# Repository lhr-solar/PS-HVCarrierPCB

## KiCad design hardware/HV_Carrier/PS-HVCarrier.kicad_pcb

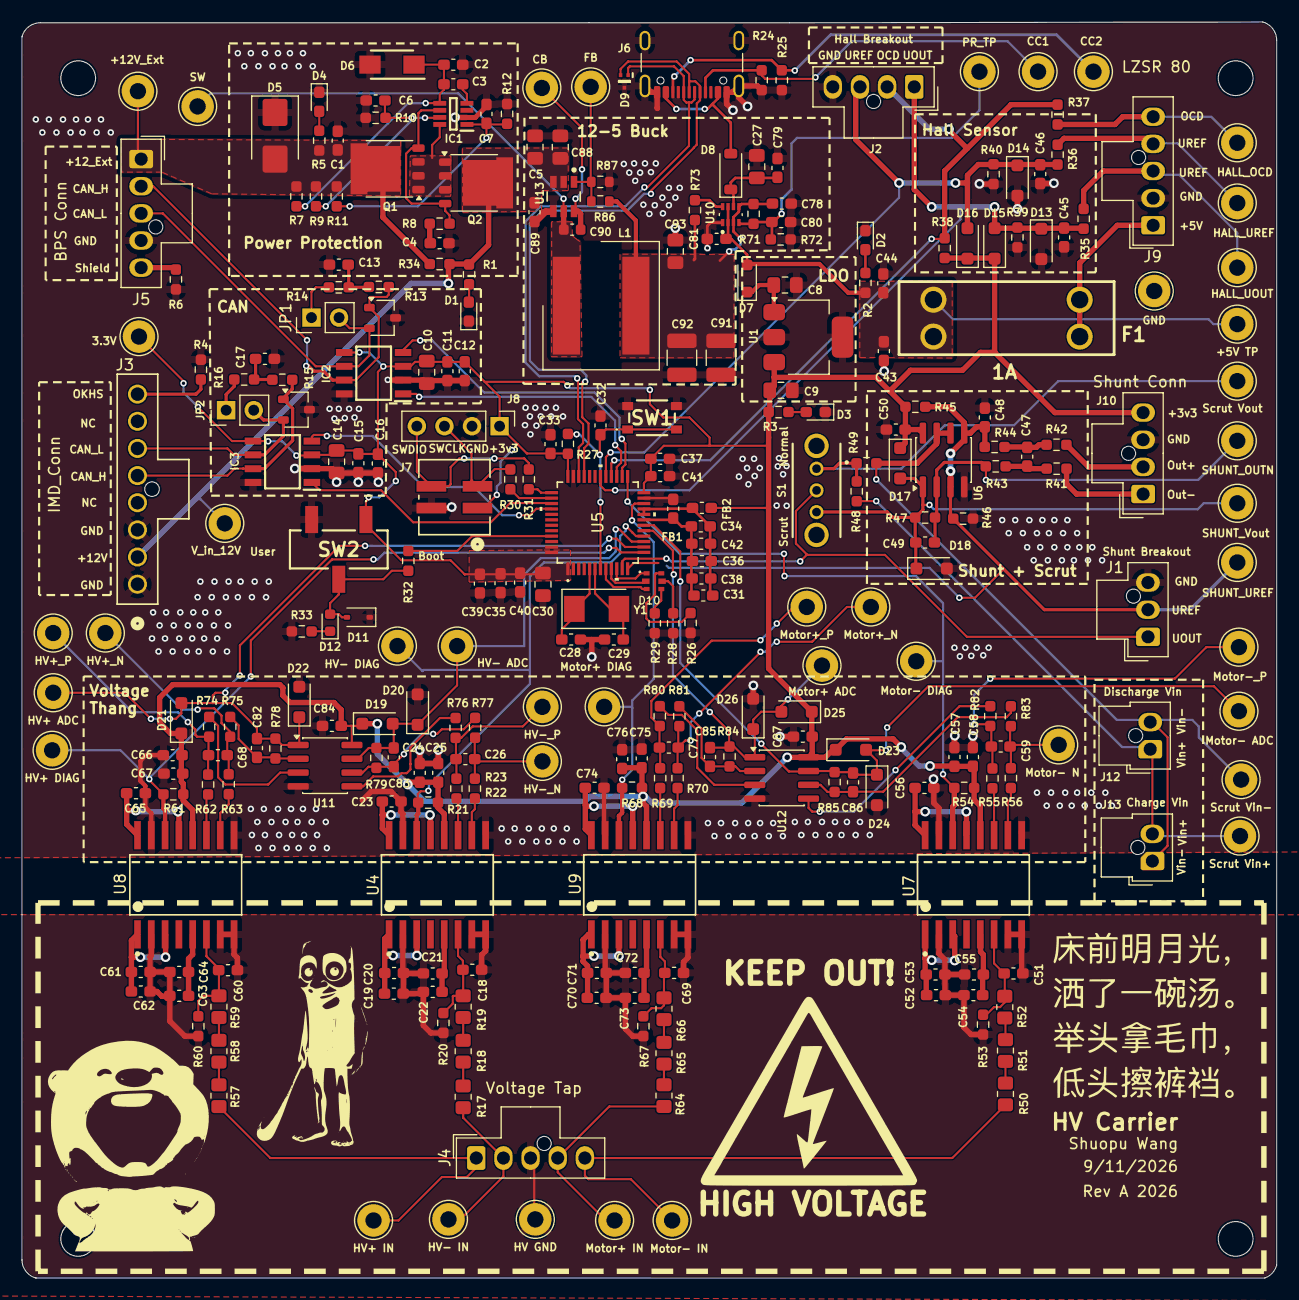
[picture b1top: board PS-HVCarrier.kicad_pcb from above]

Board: 2 copper layers, 115.6 x 115.7 mm, 291 parts (0 on the bottom side), 140 nets.

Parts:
C1, C6, C7, C11, C12, C13, C15, C16, C17, C50, C84, C87: 0.1u; C_0603_1608Metric_Pad1.08x0.95mm_HandSolder
C2, C25, C44, C58, C67, C76: 1u; C_0603_1608Metric_Pad1.08x0.95mm_HandSolder
C3: 220n; C_0603_1608Metric_Pad1.08x0.95mm_HandSolder
C4, C26, C45, C46, C59, C68, C77: 10n; C_0603_1608Metric_Pad1.08x0.95mm_HandSolder
C5, C8, C9, C10, C14, C27, C30: 10u; C_0805_2012Metric_Pad1.18x1.45mm_HandSolder
C18, C51, C60, C69: 100p; C_0603_1608Metric_Pad1.08x0.95mm_HandSolder
C19, C22, C24, C49, C52, C55, C57, C61, C64, C66, C70, C73, C75, C82, C83, C85, C86: 1n; C_0603_1608Metric_Pad1.08x0.95mm_HandSolder
C20, C21, C23, C42, C43, C47, C48, C53, C54, C56, C62, C63, C65, C71, C72, C74, C89: 100n; C_0603_1608Metric_Pad1.08x0.95mm_HandSolder
C28, C29: 26p; C_0603_1608Metric_Pad1.08x0.95mm_HandSolder
C31, C32, C33, C34, C35, C37, C39, C40, C41, C78, C79, C80, C81: 0.1uF; C_0603_1608Metric_Pad1.08x0.95mm_HandSolder
C36, C38: 1uF; C_0603_1608Metric_Pad1.08x0.95mm_HandSolder
C88: 4.7u; C_0805_2012Metric_Pad1.18x1.45mm_HandSolder
C90: 100n; C_0603_1608Metric
C91, C92: 22u; C_1210_3225Metric_Pad1.33x2.70mm_HandSolder
C93: 3.3u; C_0805_2012Metric_Pad1.18x1.45mm_HandSolder
D1, D2, D3, D4: LED; LED_0603_1608Metric_Pad1.05x0.95mm_HandSolder
D5: SMBJ15CA; D_SMB
D6: SMAF4758A; SODFL5026X125N
D7: SBA130CH-AU_R1_000A1; D_SOD-323_HandSoldering
D8: D_Schottky; D_SOD-123
D9: TPD2EUSB30DRTR
D10: RGB_LED
D11: TVS; D_SOD-323
D12: LED; LED_0603_1608Metric
D13, D14, D15, D16: D_SOD-123F
D17, D18, D19, D20, D21, D22, D23, D24, D25, D26: TVS; D_SOD-123F
F1: 1A; Fuse-3557-2
FB1, FB2: FerriteBead; C_0603_1608Metric_Pad1.08x0.95mm_HandSolder
H1, H2, H3, H4: MountingHole; MountingHole_3.2mm_M3
IC1: LM74502DDFR
IC2, IC3: TCAN3413DR
J1: Shunt Breakout; Molex_Nano-Fit_105309-xx03_1x03_P2.50mm_Vertical
J2: Hall Breakout; Molex_Nano-Fit_105309-xx04_1x04_P2.50mm_Vertical
J3: IMD_Conn; CONN_SD-105309-100_08_MOL
J4: Voltage Tap; Molex_Nano-Fit_105309-xx05_1x05_P2.50mm_Vertical
J5: BPS Conn; Molex_Nano-Fit_105309-xx05_1x05_P2.50mm_Vertical
J6: USB_C_Receptacle_USB2.0_16P; USB_C_Receptacle_GCT_USB4105-xx-A_16P_TopMnt_Horizontal
J7: SWD_Header; SWD_Conn
J8: SWD; PinHeader_1x04_P2.54mm_Vertical
J9: LZSR 80; Molex_Nano-Fit_105309-xx05_1x05_P2.50mm_Vertical
J10: Shunt Conn; Molex_Nano-Fit_105309-xx04_1x04_P2.50mm_Vertical
J12: Discharge Vin; Molex_Nano-Fit_105309-xx02_1x02_P2.50mm_Vertical
J13: Charge Vin; Molex_Nano-Fit_105309-xx02_1x02_P2.50mm_Vertical
JP1, JP2: TRM; PinHeader_1x02_P2.54mm_Vertical
L1: 8.2u; 74439369082
Q1, Q2: PSMN012-100YS; LFPAK56
R1, R5: 470; R_0603_1608Metric_Pad0.98x0.95mm_HandSolder
R2, R3: 150; R_0603_1608Metric_Pad0.98x0.95mm_HandSolder
R4: 2.1k; R_0603_1608Metric_Pad0.98x0.95mm_HandSolder
R6, R34: 0; R_0603_1608Metric_Pad0.98x0.95mm_HandSolder
R7, R27, R32, R35, R36, R37, R43, R44, R47, R49, R73, R74, R75, R76, R77, R78, R79, R80, R81, R82, R83, R84, R85: 10k; R_0603_1608Metric_Pad0.98x0.95mm_HandSolder
R8: 33; R_0603_1608Metric_Pad0.98x0.95mm_HandSolder
R9, R11: 100k; R_0603_1608Metric_Pad0.98x0.95mm_HandSolder
R10: 7.32k; R_0603_1608Metric_Pad0.98x0.95mm_HandSolder
R12: 15.8k; R_0603_1608Metric_Pad0.98x0.95mm_HandSolder
R13, R14, R15, R16: 60; R_0603_1608Metric_Pad0.98x0.95mm_HandSolder
R17, R18, R19, R50, R51, R52, R57, R58, R59, R64, R65, R66: 500k; R_0805_2012Metric_Pad1.20x1.40mm_HandSolder
R20, R38, R39, R40, R45, R46, R53, R60, R67: 20k; R_0603_1608Metric_Pad0.98x0.95mm_HandSolder
R21, R54, R61, R68: 47k; R_0603_1608Metric_Pad0.98x0.95mm_HandSolder
R22, R23, R55, R56, R62, R63, R69, R70: 10; R_0603_1608Metric_Pad0.98x0.95mm_HandSolder
R24, R25: 5.1k; R_0603_1608Metric_Pad0.98x0.95mm_HandSolder
R26, R28, R29, R33: 1k; R_0603_1608Metric_Pad0.98x0.95mm_HandSolder
R30, R31: 22; R_0603_1608Metric_Pad0.98x0.95mm_HandSolder
R41, R42: 100; R_0603_1608Metric_Pad0.98x0.95mm_HandSolder
R48: 90k; R_0603_1608Metric_Pad0.98x0.95mm_HandSolder
R71: 16k; R_0603_1608Metric_Pad0.98x0.95mm_HandSolder
R72: 4.7k; R_0603_1608Metric_Pad0.98x0.95mm_HandSolder
R86: 100k; R_0603_1608Metric
R87: 19.1k; R_0603_1608Metric
S1: OS102011MS2QN1; OS102011MA1QN1
SW1: Reset; TL3365AF180QG
SW2: SW_SPDT; BootSW
TP1: HV GND; TestPoint_THTPad_D3.0mm_Drill1.5mm
TP3: +5V TP; TestPoint_THTPad_D3.0mm_Drill1.5mm
TP4: GND; TestPoint_THTPad_D3.0mm_Drill1.5mm
TP5: +12V_Ext; TestPoint_THTPad_D3.0mm_Drill1.5mm
TP7: CC1; TestPoint_THTPad_D3.0mm_Drill1.5mm
TP8: CC2; TestPoint_THTPad_D3.0mm_Drill1.5mm
TP9: PR_TP; TestPoint_THTPad_D3.0mm_Drill1.5mm
TP10: HALL_UOUT; TestPoint_THTPad_D3.0mm_Drill1.5mm
TP11: HALL_UREF; TestPoint_THTPad_D3.0mm_Drill1.5mm
TP12: HALL_OCD; TestPoint_THTPad_D3.0mm_Drill1.5mm
TP13: SHUNT_OUTN; TestPoint_THTPad_D3.0mm_Drill1.5mm
TP14: SHUNT_UREF; TestPoint_THTPad_D3.0mm_Drill1.5mm
TP15: Scrut Vin+; TestPoint_THTPad_D3.0mm_Drill1.5mm
TP16: Scrut Vout; TestPoint_THTPad_D3.0mm_Drill1.5mm
TP17: Scrut Vin-; TestPoint_THTPad_D3.0mm_Drill1.5mm
TP18: SHUNT_Vout; TestPoint_THTPad_D3.0mm_Drill1.5mm
TP19: HV+ IN; TestPoint_THTPad_D3.0mm_Drill1.5mm
TP20: Motor+ IN; TestPoint_THTPad_D3.0mm_Drill1.5mm
TP21: HV+_P; TestPoint_THTPad_D3.0mm_Drill1.5mm
TP22: HV+_N; TestPoint_THTPad_D3.0mm_Drill1.5mm
TP23: Motor+_P; TestPoint_THTPad_D3.0mm_Drill1.5mm
TP24: Motor+_N; TestPoint_THTPad_D3.0mm_Drill1.5mm
TP25: HV+ DIAG; TestPoint_THTPad_D3.0mm_Drill1.5mm
TP26: Motor+ DIAG; TestPoint_THTPad_D3.0mm_Drill1.5mm
TP27: Motor- IN; TestPoint_THTPad_D3.0mm_Drill1.5mm
TP28: HV- IN; TestPoint_THTPad_D3.0mm_Drill1.5mm
TP29: HV-_P; TestPoint_THTPad_D3.0mm_Drill1.5mm
TP30: HV-_N; TestPoint_THTPad_D3.0mm_Drill1.5mm
TP31: Motor-_P; TestPoint_THTPad_D3.0mm_Drill1.5mm
TP32: Motor- N; TestPoint_THTPad_D3.0mm_Drill1.5mm
TP33: HV- DIAG; TestPoint_THTPad_D3.0mm_Drill1.5mm
TP34: Motor- DIAG; TestPoint_THTPad_D3.0mm_Drill1.5mm
TP35: HV- ADC; TestPoint_THTPad_D3.0mm_Drill1.5mm
TP36: HV+ ADC; TestPoint_THTPad_D3.0mm_Drill1.5mm
TP37: Motor+ ADC; TestPoint_THTPad_D3.0mm_Drill1.5mm
TP38: Motor- ADC; TestPoint_THTPad_D3.0mm_Drill1.5mm
TP39: V_in_12V; TestPoint_THTPad_D3.0mm_Drill1.5mm
TP40: CB; TestPoint_THTPad_D3.0mm_Drill1.5mm
TP41: FB; TestPoint_THTPad_D3.0mm_Drill1.5mm
TP42: SW; TestPoint_THTPad_D3.0mm_Drill1.5mm
TP_1: 3.3V; TestPoint_THTPad_D3.0mm_Drill1.5mm
U1: MCP1826S; SOT-223-3_TabPin2
U2, U3: CDSOT23-T24CAN
U4, U7, U8, U9: AMC3311QDWERQ1; DWE0016A-IPC_A
U5: STM32G473CETx; 48PinMCU
U6, U11, U12: TLV9002QDRQ1; SOIC-8_3.9x4.9mm_P1.27mm
U10: TPS2117DRLR
U13: LMR51635XDDCR; DDC0006A-MFG
Y1: Crystal; Crystal_SMD_Abracon_ABM3-2Pin_5.0x3.2mm

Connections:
/48PinMCU/BOOT0: R32.1, U5.45 (PB8-BOOT0)
/48PinMCU/GNDA: C31.2, C34.2, C36.2, C38.2, C42.2, FB1.1, U5.19 (VSSA)
/48PinMCU/NRST: C32.1, R27.1, SW1.1, U5.7 (PG10-NRST)
/48PinMCU/PA0: D10.5, U5.8 (PA0-GPIO_BLUE)
/48PinMCU/PA1: D10.3, U5.9 (PA1_GPIO_RED)
/48PinMCU/PA2: D10.1, U5.10 (PA2-GPIO_GREEN)
/48PinMCU/SWCLK: R30.1, U5.38 (PA14)
/48PinMCU/SWDIO: R31.1, U5.37 (PA13)
/48PinMCU/VDDA: C31.1, C34.1, C36.1, C38.1, C42.1, FB2.2, U5.20 (VREF+), U5.21 (VDDA)
/+3v3: C9.2, C10.1, C11.1, C12.1, C14.1, C15.1, C16.1, C24.1, C25.1, C30.1, C33.1, C35.1, C37.1, C39.1, C40.1, C41.1, C50.1, C57.1, C58.1, C66.1, C67.1, C75.1, C76.1, C84.1, C87.1, D15.1 (K), D16.1 (K), D17.1 (K), D19.1 (K), D21.1 (K), D23.1 (K), D25.1 (K), FB2.1, IC2.3 (VCC), IC2.5 (SHDNV_IO), IC3.3 (VCC), IC3.5 (SHDNV_IO), J7.1, J8.1, J10.4 (PWR), R3.1, R21.1, R27.2, R38.2, R45.2, R54.1, R61.1, R68.1, SW2.1 (A), TP_1.1 (1_1), U1.3 (VO), U4.12 (VDD), U5.1 (VBAT), U5.24 (VDD), U5.36 (VDD), U5.48 (VDD), U6.8 (V+), U7.12 (VDD), U8.12 (VDD), U9.12 (VDD), U11.8 (V+), U12.8 (V+)
/+5V: C43.1, C44.1, C81.1, D7.2 (A), F1.1, R2.1, TP3.1 (1_1), U10.2 (VOUT), U10.7 (VOUT__1)
/+12V: C5.1, C88.1, C89.1, J3.2, Q2.5, R1.1, R34.2, TP39.1 (1_1), U13.2 (EN), U13.3 (VIN)
/+12V_Ext: C1.1, D5.2 (A2), J5.1 (12V), Q1.5, R5.1, R7.2, R9.1, R11.1, R34.1, TP5.1 (1_1)
/BPS_CAN_H: IC2.7 (CANH), J5.2 (CAN_H), R13.1, U2.1 (CAN_H)
/BPS_CAN_L: IC2.6 (CANL), J5.3 (CAN_L), JP1.2 (B), U2.2 (CAN_L)
/CAN1_RX: IC3.4 (RXD), U5.40 (PB3)
/CAN1_TX: IC3.1 (TXD), U5.39 (PA15)
/CAN2_RX: IC2.4 (RXD), U5.26 (PB12)
/CAN2_TX: IC2.1 (TXD), U5.27 (PB13)
/Current_Sense/LZSR_OCD: J9.5 (OCD), R37.2, TP12.1 (1_1)
/Current_Sense/LZSR_UOUT: J9.3 (UOUT), R35.2, TP10.1 (1_1)
/Current_Sense/LZSR_UREF: J9.4 (UREF), R36.2, TP11.1 (1_1)
/Current_Sense/SHUNT Vout: C49.1, D17.2 (A), D18.1 (K), R47.1, S1.3, TP18.1 (1_1), U6.1
/Current_Sense/Scrut Vout: R48.2, R49.1, S1.1, TP16.1 (1_1)
/Current_Sense/Vin+: J12.1, J13.2, R48.1, TP15.1 (1_1)
/Current_Sense/Vin-: J12.2, J13.1, R49.2, TP17.1 (1_1), U6.6 (-), U6.7
/HALL_OCD: J2.2 (UREF), R37.1, R38.1, U5.28 (PB14)
/HALL_UOUT: C45.1, D13.1 (K), D15.2 (A), J2.1 (UOUT), R35.1, R39.2, U5.30 (PA8)
/HALL_UREF: C46.1, D14.1 (K), D16.2 (A), J2.3 (GND), R36.1, R40.2, U5.29 (PB15)
/HV+: J4.1 (HV+), R57.1, TP19.1 (1_1)
/HV+_ADC: C82.2, D21.2 (A), D22.1 (K), R78.1, TP36.1 (1_1), U5.14 (PA6), U11.1
/HV+_DIAG: R61.2, TP25.1 (1_1), U5.13 (PA5), U8.14 (DIAG)
/HV-: J4.2 (HV-), R17.1, TP28.1 (1_1)
/HV-_ADC: C83.2, D19.2 (A), D20.1 (K), R79.1, TP35.1 (1_1), U5.15 (PA7), U11.7
/HV-_DIAG: R21.2, TP33.1 (1_1), U4.14 (DIAG), U5.16 (PB0)
/IMD_CAN_H: IC3.7 (CANH), J3.5, R15.1, U3.1 (CAN_H)
/IMD_CAN_L: IC3.6 (CANL), J3.6, JP2.2 (B), U3.2 (CAN_L)
/IMD_OKHS: J3.8, R4.2
/MOTOR+_ADC: C85.2, D25.2 (A), D26.1 (K), R84.1, TP37.1 (1_1), U5.17 (PB1), U12.1
/MOTOR+_DIAG: R68.2, TP26.1 (1_1), U5.22 (PB10), U9.14 (DIAG)
/MOTOR-_ADC: C86.2, D23.2 (A), D24.1 (K), R85.1, TP38.1 (1_1), U5.18 (PB2), U12.7
/MOTOR-_DIAG: R54.2, TP34.1 (1_1), U5.25 (PB11), U7.14 (DIAG)
/Motor_Precharge+: J4.4 (MOTOR+), R64.1, TP20.1 (1_1)
/Motor_Precharge-: J4.5 (MOTOR-), R50.1, TP27.1 (1_1)
/Power_Data/12VBuck/CB: C90.1, TP40.1 (1_1), U13.6 (CB)
/Power_Data/12VBuck/FB: R86.2, R87.1, TP41.1 (1_1), U13.1 (FB)
/Power_Data/12VBuck/SW: C90.2, L1.1, TP42.1 (1_1), U13.5 (SW)
/Power_Data/Buck_5V: C78.1, C91.1, C92.1, C93.1, L1.2, R71.1, R73.1, R86.1, U10.3 (VIN1), U10.5 (MODE)
/Power_Data/PowerProtection/EN/UVLO: C7.2, IC1.1 (EN/UVLO), R11.2, R12.2
/Power_Data/PowerProtection/OV: C6.2, IC1.7 (OV), R9.2, R10.1
/Power_Data/PowerProtection/gate: IC1.6 (GATE), Q1.4, Q2.4, R8.2
/Power_Data/PowerProtection/source: IC1.8 (SRC), Q1.1, Q1.2, Q1.3, Q2.1, Q2.2, Q2.3
/Power_Data/Power_Mux/PR1: C80.1, R71.2, R72.1, TP9.1 (1_1), U10.4 (PR1)
/Power_Data/Power_Mux/VIN_2: C27.2, C79.1, D8.1 (K), U10.6 (VIN2)
/Power_Data/USB-C Connector/CC1: J6.A5 (CC1), R24.2, TP7.1 (1_1)
/Power_Data/USB-C Connector/CC2: J6.B5 (CC2), R25.2, TP8.1 (1_1)
/Power_Data/USB-C Connector/VBUS_IN: D8.2 (A), J6.A4 (VBUS), J6.A9 (VBUS), J6.B4 (VBUS), J6.B9 (VBUS)
/SHUNT_UOUT: J1.1 (UOUT), S1.2, U5.11 (PA3)
/SHUNT_UREF: C48.1, J1.2 (UREF), R44.1, R45.1, R46.1, TP14.1 (1_1), U5.12 (PA4), U6.3 (+), U6.5 (+)
/USB_D+: D9.1 (D+), J6.A6 (D+), J6.B6 (D+), U5.34 (PA12)
/USB_D-: D9.2 (D-), J6.A7 (D-), J6.B7 (D-), U5.33 (PA11)
/Voltage_Sense/HV+_N: C68.1, R63.2, R75.1, TP22.1 (1_1)
/Voltage_Sense/HV+_P: C68.2, R62.2, R74.1, TP21.1 (1_1)
/Voltage_Sense/HV-_N: C26.1, R23.2, R77.1, TP30.1 (1_1)
/Voltage_Sense/HV-_P: C26.2, R22.2, R76.1, TP29.1 (1_1)
/Voltage_Sense/Motor+_N: C77.1, R70.2, R81.1, TP24.1 (1_1)
/Voltage_Sense/Motor+_P: C77.2, R69.2, R80.1, TP23.1 (1_1)
/Voltage_Sense/Motor-_N: C59.1, R56.2, R83.1, TP32.1 (1_1)
/Voltage_Sense/Motor-_P: C59.2, R55.2, R82.1, TP31.1 (1_1)
GND: C1.2, C2.1, C4.2, C5.2, C6.1, C7.1, C8.1, C9.1, C10.2, C11.2, C12.2, C13.2, C14.2, C15.2, C16.2, C17.2, C23.2, C24.2, C25.2, C27.1, C28.1, C29.2, C30.2, C32.2, C33.2, C35.2, C37.2, C39.2, C40.2, C41.2, C43.2, C44.2, C45.2, C46.2, C48.2, C50.2, C56.2, C57.2, C58.2, C65.2, C66.2, C67.2, C74.2, C75.2, C76.2, C78.2, C79.2, C80.2, C81.2, C84.2, C87.2, C88.2, C89.2, C91.2, C92.2, C93.2, D1.1 (K), D2.1 (K), D3.1 (K), D4.1 (K), D5.1 (A1), D6.2 (A), D9.3 (GND), D11.1 (A1), D13.2 (A), D14.2 (A), D18.2 (A), D20.2 (A), D22.2 (A), D24.2 (A), D26.2 (A), FB1.2, IC1.2 (GND), IC2.2 (GND), IC2.8 (STB), IC3.2 (GND), IC3.8 (STB), J1.3 (GND), J2.4 (GND), J3.1, J3.3, J5.4 (GND), J6.A1 (GND), J6.A12 (GND), J6.B1 (GND), J6.B12 (GND), J6.S1 (SHIELD), J6.S2 (Shield), J6.S3 (Shield), J6.S4 (Shield), J7.2, J8.2, J9.2 (GND), J10.3 (GND), R4.1, R6.1, R10.2, R12.1, R24.1, R25.1, R26.2, R28.2, R29.2, R33.2, R39.1, R40.1, R46.2, R72.2, R87.2, SW1.2, SW2.3 (C), TP4.1 (1_1), U1.2 (GND), U2.3 (GND), U3.3 (GND), U4.9 (GND), U4.15 (DCDC_GND), U5.23 (VSS), U5.35 (VSS), U5.47 (VSS), U6.4 (V-), U7.9 (GND), U7.15 (DCDC_GND), U8.9 (GND), U8.15 (DCDC_GND), U9.9 (GND), U9.15 (DCDC_GND), U10.1 (GND), U11.4 (V-), U12.4 (V-), U13.4 (GND)
HV GND: C18.2, C19.2, C20.1, C21.1, C22.1, C51.2, C52.2, C53.1, C54.1, C55.1, C60.2, C61.2, C62.1, C63.1, C64.1, C69.2, C70.2, C71.1, C72.1, C73.1, J4.3 (GND), R20.1, R53.1, R60.1, R67.1, TP1.1 (1_1), U4.2 (DCDC_HGND), U4.7 (HGND), U4.8 (HGND), U7.2 (DCDC_HGND), U7.7 (HGND), U7.8 (HGND), U8.2 (DCDC_HGND), U8.7 (HGND), U8.8 (HGND), U9.2 (DCDC_HGND), U9.7 (HGND), U9.8 (HGND)
unnamed: C4.1, R8.1
unnamed: C13.1, R13.2, R14.1
unnamed: C17.1, R15.2, R16.1
unnamed: C47.1, R41.1, R43.2
unnamed: C47.2, R42.1, R44.2
unnamed: D1.2 (A), R1.2
unnamed: D2.2 (A), R2.2
unnamed: D3.2 (A), R3.2
unnamed: D4.2 (A), R5.2
unnamed: C2.2, C3.1, D6.1 (K), IC1.5 (VS), R7.1
unnamed: C8.2, D7.1 (K), U1.1 (VI)
unnamed: D10.2, R26.1
unnamed: D10.4, R28.1
unnamed: D10.6, R29.1
unnamed: D11.2 (A2), D12.2 (A), R32.2, SW2.2 (B)
unnamed: D12.1 (K), R33.1
unnamed: C3.2, IC1.4 (VCAP)
unnamed: J5.5 (SHIELD), R6.2
unnamed: J7.3, J8.3, R30.2
unnamed: J7.4, J8.4, R31.2
unnamed: F1.2, J9.1 (+UC)
unnamed: J10.2 (Out+), R42.2
unnamed: J10.1 (Out-), R41.2
unnamed: JP1.1 (A), R14.2
unnamed: JP2.1 (A), R16.2
unnamed: R17.2, R18.1
unnamed: R18.2, R19.1
unnamed: R50.2, R51.1
unnamed: R51.2, R52.1
unnamed: R57.2, R58.1
unnamed: R58.2, R59.1
unnamed: R64.2, R65.1
unnamed: R65.2, R66.1
unnamed: C23.1, U4.13 (LDO_OUT), U4.16 (DCDC_IN)
unnamed: C19.1, C20.2, U4.1 (DCDC_OUT), U4.3 (HLDO_IN)
unnamed: C21.2, C22.2, U4.5 (HLDO_OUT)
unnamed: C18.1, R19.2, R20.2, U4.6 (IN)
unnamed: R23.1, U4.10 (OUTN)
unnamed: R22.1, U4.11 (OUTP)
unnamed: C28.2, U5.5 (PF0-OSC_IN), Y1.1
unnamed: C29.1, U5.6 (PF1-OSC_OUT), Y1.2
unnamed: C49.2, R43.1, R47.2, TP13.1 (1_1), U6.2 (-)
unnamed: C56.1, U7.13 (LDO_OUT), U7.16 (DCDC_IN)
unnamed: C52.1, C53.2, U7.1 (DCDC_OUT), U7.3 (HLDO_IN)
unnamed: C54.2, C55.2, U7.5 (HLDO_OUT)
unnamed: C51.1, R52.2, R53.2, U7.6 (IN)
unnamed: R56.1, U7.10 (OUTN)
unnamed: R55.1, U7.11 (OUTP)
unnamed: C65.1, U8.13 (LDO_OUT), U8.16 (DCDC_IN)
unnamed: C61.1, C62.2, U8.1 (DCDC_OUT), U8.3 (HLDO_IN)
unnamed: C63.2, C64.2, U8.5 (HLDO_OUT)
unnamed: C60.1, R59.2, R60.2, U8.6 (IN)
unnamed: R63.1, U8.10 (OUTN)
unnamed: R62.1, U8.11 (OUTP)
unnamed: C74.1, U9.13 (LDO_OUT), U9.16 (DCDC_IN)
unnamed: C70.1, C71.2, U9.1 (DCDC_OUT), U9.3 (HLDO_IN)
unnamed: C72.2, C73.2, U9.5 (HLDO_OUT)
unnamed: C69.1, R66.2, R67.2, U9.6 (IN)
unnamed: R70.1, U9.10 (OUTN)
unnamed: R69.1, U9.11 (OUTP)
unnamed: R73.2, U10.8 (ST)
unnamed: R74.2, U11.3 (+)
unnamed: C82.1, R75.2, R78.2, U11.2 (-)
unnamed: R76.2, U11.5 (+)
unnamed: C83.1, R77.2, R79.2, U11.6 (-)
unnamed: R80.2, U12.3 (+)
unnamed: C85.1, R81.2, R84.2, U12.2 (-)
unnamed: R82.2, U12.5 (+)
unnamed: C86.1, R83.2, R85.2, U12.6 (-)

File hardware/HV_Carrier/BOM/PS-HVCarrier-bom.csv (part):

"Reference","Qty","Value","DNP","Footprint","LCSC P/N","P/N"
"C1,C6,C7,C11,C12,C13,C15,C16,C17,C50,C84,C87","12","0.1u","","Capacitor_SMD:C_0603_1608Metric_Pad1.08x0.95mm_HandSolder","C14663","MLASH168SB7104KTNA01"
"C2,C25,C44,C58,C67,C76","6","1u","","Capacitor_SMD:C_0603_1608Metric_Pad1.08x0.95mm_HandSolder","C15849","MLASU168SB5105KTNA01"
"C3","1","220n","","Capacitor_SMD:C_0603_1608Metric_Pad1.08x0.95mm_HandSolder","C344195","MSASU168SB7224KTNB25"
"C4,C26,C45,C46,C59,C68,C77","7","10n","","Capacitor_SMD:C_0603_1608Metric_Pad1.08x0.95mm_HandSolder","","MSASH168SB5103KTNA01"
"C5,C8,C9,C10,C14,C27,C30","7","10u","","Capacitor_SMD:C_0805_2012Metric_Pad1.18x1.45mm_HandSolder","C440198","GRM21BR61H106KE43K"
"C18,C51,C60,C69","4","100p","","Capacitor_SMD:C_0603_1608Metric_Pad1.08x0.95mm_HandSolder","","MMARQ167SCG101JTRA18 "
"C19,C22,C24,C49,C52,C55,C57,C61,C64,C66,C70,C73,C75,C82,C83,C85,C86","17","1n","","Capacitor_SMD:C_0603_1608Metric_Pad1.08x0.95mm_HandSolder","","MLASU063SB7102KFNA01"
"C20,C21,C23,C42,C43,C47,C48,C53,C54,C56,C62,C63,C65,C71,C72,C74,C89","17","100n","","Capacitor_SMD:C_0603_1608Metric_Pad1.08x0.95mm_HandSolder","C15849","MLASH168SB7104KTNA01"
"C28,C29","2","26p","","Capacitor_SMD:C_0603_1608Metric_Pad1.08x0.95mm_HandSolder","C92670","0603N270F500CT "
"C31,C32,C33,C34,C35,C37,C39,C40,C41,C78,C79,C80,C81","13","0.1uF","","Capacitor_SMD:C_0603_1608Metric_Pad1.08x0.95mm_HandSolder","C14663","MLASH168SB7104KTNA01"
"C36,C38","2","1uF","","Capacitor_SMD:C_0603_1608Metric_Pad1.08x0.95mm_HandSolder","C15849","MLASU168SB5105KTNA01"
"C88","1","4.7u","","Capacitor_SMD:C_0805_2012Metric_Pad1.18x1.45mm_HandSolder","C6962403","08055D475KAT4A"
"C90","1","100n","","Capacitor_SMD:C_0603_1608Metric","C6666325","MLASH168SB7104KTNA01"
"C91,C92","2","22u","","Capacitor_SMD:C_1210_3225Metric_Pad1.33x2.70mm_HandSolder","C778721","GMK325BJ226MM-P"
"C93","1","3.3u","","Capacitor_SMD:C_0805_2012Metric_Pad1.18x1.45mm_HandSolder","C342775","C2012X5R1H335K125AB"
"D1,D2,D3,D4","4","LED","","LED_SMD:LED_0603_1608Metric_Pad1.05x0.95mm_HandSolder","","NCD0603R1"
"D5","1","SMBJ15CA","","Diode_SMD:D_SMB","C669039","SMBJ15CA"
"D6","1","SMAF4758A","","LHRS_Passives:SODFL5026X125N","","SMAF4758A"
"D7","1","SBA130CH-AU_R1_000A1","","Diode_SMD:D_SOD-323_HandSoldering","C191023","SBA130CH-AU_R1_000A1 "
"D8","1","D_Schottky","","Diode_SMD:D_SOD-123","C82544","BAT760-7"
"D9","1","TPD2EUSB30DRTR","","LHRS_ICs:TPD2EUSB30DRTR","C97502","TPD2EUSB30DRTR"
"D10","1","RGB_LED","","LHRS_Special:RGB_LED","C264519","19-337/R6GHBHC-A01/2T "
"D11","1","TVS","","Diode_SMD:D_SOD-323","C725495","PESD15VL1BA"
"D12","1","LED","","LED_SMD:LED_0603_1608Metric","C125103","LTST-C193TBKT-5A"
"D13,D14,D15,D16","4","","","Diode_SMD:D_SOD-123F","","576-SMF3.3"
"D17,D18,D19,D20,D21,D22,D23,D24,D25,D26","10","TVS","","Diode_SMD:D_SOD-123F","","576-SMF3.3"
"F1","1","1A","","LHRS_Power:Fuse-3557-2","C3205238","3557-2"
"FB1,FB2","2","FerriteBead","","Capacitor_SMD:C_0603_1608Metric_Pad1.08x0.95mm_HandSolder","C354394","BLM18PG121SH1D"
"IC1","1","LM74502DDFR","","LHRS_Power:LM74502DDFR","C3236215","LM74502DDFR"
"IC2,IC3","2","TCAN3413DR","","LHRS_Passives:TCAN3413DR","C22433320","TCAN3413DR"
"J1","1","Shunt Breakout","","LHRS_Connectors:Molex_Nano-Fit_105309-xx03_1x03_P2.50mm_Vertical","","1053091103"
"J2","1","Hall Breakout","","LHRS_Connectors:Molex_Nano-Fit_105309-xx04_1x04_P2.50mm_Vertical","","1053091104"
"J3","1","IMD_Conn","","1053091108:CONN_SD-105309-100_08_MOL","","IPD1-08-S-K "
"J4","1","Voltage Tap","","LHRS_Connectors:Molex_Nano-Fit_105309-xx05_1x05_P2.50mm_Vertical","","1053091105"
"J5","1","BPS Conn","","LHRS_Connectors:Molex_Nano-Fit_105309-xx05_1x05_P2.50mm_Vertical","","1053091105"
"J6","1","USB_C_Receptacle_USB2.0_16P","","LHRS_Connectors:USB_C_Receptacle_GCT_USB4105-xx-A_16P_TopMnt_Horizontal","","USB4105-GF-A-120"
"J7","1","SWD_Header","","LHRS_Connectors:SWD_Conn","","0878320406"
"J8","1","SWD","","Connector_PinHeader_2.54mm:PinHeader_1x04_P2.54mm_Vertical","",""
"J9","1","LZSR 80-P","","LHRS_Connectors:Molex_Nano-Fit_105309-xx05_1x05_P2.50mm_Vertical","","1053091105"
"J10","1","Shunt Conn","","LHRS_Connectors:Molex_Nano-Fit_105309-xx04_1x04_P2.50mm_Vertical","","1053091104"
"J11","1","SSA-2-100A","DNP","","","1053071204"
"J12","1","Discharge Vin","","LHRS_Connectors:Molex_Nano-Fit_105309-xx02_1x02_P2.50mm_Vertical","","1053091102"
"J13","1","Charge Vin","","LHRS_Connectors:Molex_Nano-Fit_105309-xx02_1x02_P2.50mm_Vertical","","1053091102"
"JP1,JP2","2","TRM","","Connector_PinHeader_2.54mm:PinHeader_1x02_P2.54mm_Vertical","",""
"L1","1","8.2u","","LHRS_Passives:74439369082","","74439369082"
"Q1,Q2","2","PSMN012-100YS","","Package_TO_SOT_SMD:LFPAK56","C20443035","PSMN012-100YSFX"
"R1,R5","2","470","","Resistor_SMD:R_0603_1608Metric_Pad0.98x0.95mm_HandSolder","","CRCW1206470RFKEA "
"R2,R3","2","150","","Resistor_SMD:R_0603_1608Metric_Pad0.98x0.95mm_HandSolder","","CRCW0603150RFKEC"
"R4","1","2.1k","","Resistor_SMD:R_0603_1608Metric_Pad0.98x0.95mm_HandSolder","","CRCW06032K10FKEA "
"R6","1","0","DNP","Resistor_SMD:R_0603_1608Metric_Pad0.98x0.95mm_HandSolder","","CRCW06030000Z0EE"
"R7,R27,R32,R35,R36,R37,R43,R44,R47,R49,R73,R74,R75,R76,R77,R78,R79,R80,R81,R82,R83,R84,R85","23","10k","","Resistor_SMD:R_0603_1608Metric_Pad0.98x0.95mm_HandSolder","C25804","CRCW060310K0FKEI"
"R8","1","33","","Resistor_SMD:R_0603_1608Metric_Pad0.98x0.95mm_HandSolder","C844927","CRCW060333R0FKEA"
"R9,R11","2","100k","","Resistor_SMD:R_0603_1608Metric_Pad0.98x0.95mm_HandSolder","C844916","CRCW0603100KFKED"
"R10","1","7.32k","","Resistor_SMD:R_0603_1608Metric_Pad0.98x0.95mm_HandSolder","C843967","CRCW06037K32FKEA "
"R12","1","15.8k","","Resistor_SMD:R_0603_1608Metric_Pad0.98x0.95mm_HandSolder","C2090646","CRCW0603137KFKEA"
"R13,R14,R15,R16","4","60","","Resistor_SMD:R_0603_1608Metric_Pad0.98x0.95mm_HandSolder","C166918","CRCW060360R4FKEA"
"R17,R18,R19,R50,R51,R52,R57,R58,R59,R64,R65,R66","12","500k","","Resistor_SMD:R_0805_2012Metric_Pad1.20x1.40mm_HandSolder","","RNCF0805BTE500K"
"R20,R38,R39,R40,R45,R46,R53,R60,R67","9","20k","","Resistor_SMD:R_0603_1608Metric_Pad0.98x0.95mm_HandSolder","","CR0603-FX-2002ELF "
"R21,R54,R61,R68","4","47k","","Resistor_SMD:R_0603_1608Metric_Pad0.98x0.95mm_HandSolder","","CRCW060347K0FKECC"
"R22,R23,R55,R56,R62,R63,R69,R70","8","10","","Resistor_SMD:R_0603_1608Metric_Pad0.98x0.95mm_HandSolder","","CRCW060310R0FKEE"
"R24,R25","2","5.1k","","Resistor_SMD:R_0603_1608Metric_Pad0.98x0.95mm_HandSolder","C23186","0603WAF5101T5E"
"R26,R28,R29,R33","4","1k","","Resistor_SMD:R_0603_1608Metric_Pad0.98x0.95mm_HandSolder","C21190","CRCW06031K00FKEI "
"R30,R31","2","22","","Resistor_SMD:R_0603_1608Metric_Pad0.98x0.95mm_HandSolder","C2930077","RC0603FR-0722RL"
"R34","1","0","","Resistor_SMD:R_0603_1608Metric_Pad0.98x0.95mm_HandSolder","C21189","CRCW06030000Z0EE"
"R41,R42","2","100","","Resistor_SMD:R_0603_1608Metric_Pad0.98x0.95mm_HandSolder","","0603WAF1000T5E"
"R48","1","90.9k","","Resistor_SMD:R_0603_1608Metric_Pad0.98x0.95mm_HandSolder","","RMCF0603FT90K9"
"R71","1","16k","","Resistor_SMD:R_0603_1608Metric_Pad0.98x0.95mm_HandSolder","","CRCW060316K0FKTA "
"R72","1","4.7k","","Resistor_SMD:R_0603_1608Metric_Pad0.98x0.95mm_HandSolder","","CRCW06034K70FKEA"
"R86","1","100k","","Resistor_SMD:R_0603_1608Metric","C25803","CRCW0603100KFKEE"
"R87","1","19.1k","","Resistor_SMD:R_0603_1608Metric","C844132","CRCW060319K1FKEAHP"
"S1","1","OS102011MS2QN1","","OS102011MS2QN1:OS102011MA1QN1","","OS102011MS2QN1"
"SW1","1","Reset","","LHRS_Special:TL3365AF180QG","C2886926","TL3365AF180QG"
"SW2","1","SW_SPDT","","LHRS_Special:BootSW","-","450406020024"
"TP1","1","HV GND","","TestPoint:TestPoint_THTPad_D3.0mm_Drill1.5mm","",""
"TP3","1","+5V TP","","TestPoint:TestPoint_THTPad_D3.0mm_Drill1.5mm","",""
"TP4","1","GND","","TestPoint:TestPoint_THTPad_D3.0mm_Drill1.5mm","",""
"TP5","1","+12V_Ext TP","","TestPoint:TestPoint_THTPad_D3.0mm_Drill1.5mm","",""
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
